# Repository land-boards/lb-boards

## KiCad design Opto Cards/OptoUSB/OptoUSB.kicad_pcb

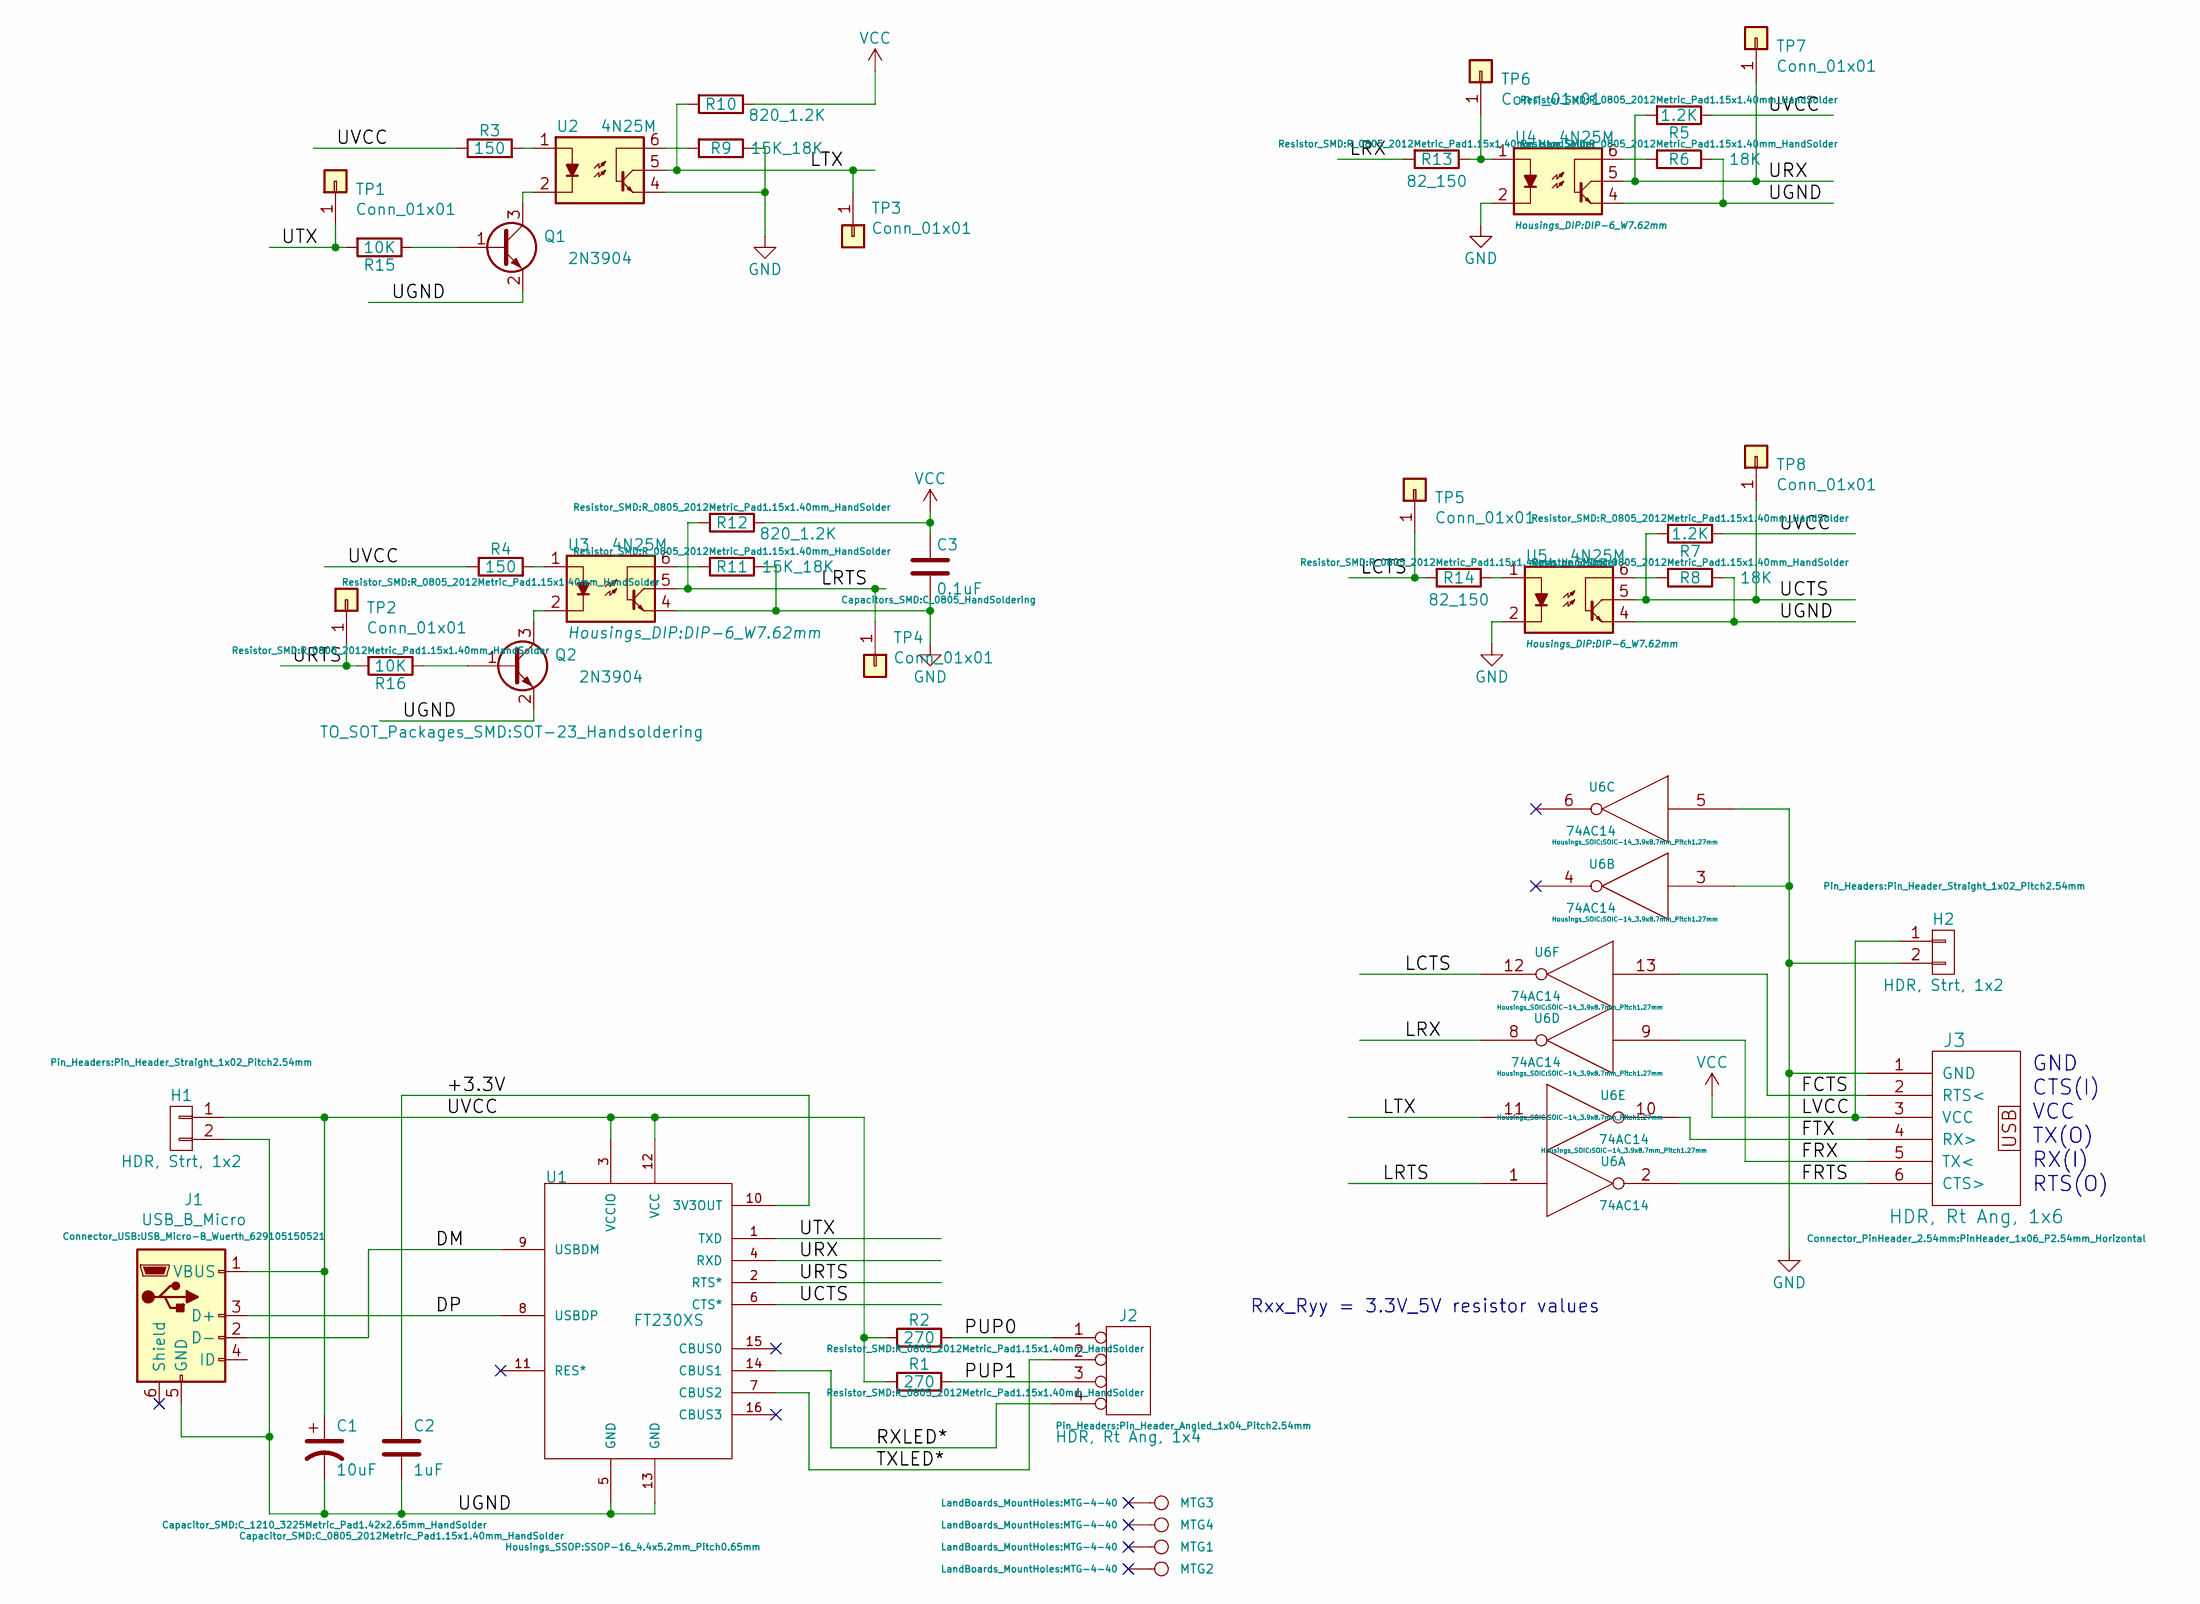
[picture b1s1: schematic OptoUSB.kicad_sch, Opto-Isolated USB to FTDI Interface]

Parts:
C1: 10uF; C_1210_3225Metric_Pad1.42x2.65mm_HandSolder; MfgPN CC121ZKY5V8BB106
C2: 1uF; C_0805_2012Metric_Pad1.15x1.40mm_HandSolder; MfgPN GRM155F51E104ZA1J
C3: 0.1uF; C_0805_HandSoldering
H1, H2: HDR, Strt, 1x2; Pin_Header_Straight_1x02_Pitch2.54mm
J1: USB_B_Micro; USB_Micro-B_Wuerth_629105150521
J2: HDR, Rt Ang, 1x4; Pin_Header_Angled_1x04_Pitch2.54mm
J3: HDR, Rt Ang, 1x6; PinHeader_1x06_P2.54mm_Horizontal
MTG1, MTG3: CONN_1; MTG-4-40; MfgPN N/A
MTG2, MTG4: CONN_1; MTG-4-40
Q1, Q2: 2N3904; SOT-23_Handsoldering
R1: 270; R_0805_2012Metric_Pad1.15x1.40mm_HandSolder
R2: 270; R_0805_2012Metric_Pad1.15x1.40mm_HandSolder; MfgPN CRG0805F270R
R3, R4: 150; R_0805_2012Metric_Pad1.15x1.40mm_HandSolder
R5, R7: 1.2K; R_0805_2012Metric_Pad1.15x1.40mm_HandSolder
R6, R8: 18K; R_0805_2012Metric_Pad1.15x1.40mm_HandSolder
R9, R11: 15K_18K; R_0805_2012Metric_Pad1.15x1.40mm_HandSolder
R10, R12: 820_1.2K; R_0805_2012Metric_Pad1.15x1.40mm_HandSolder
R13, R14: 82_150; R_0805_2012Metric_Pad1.15x1.40mm_HandSolder
R15, R16: 10K; R_0805_2012Metric_Pad1.15x1.40mm_HandSolder
TP1, TP2, TP3, TP4, TP5, TP6, TP7, TP8: Conn_01x01; PinHeader_1x01_P2.54mm_Vertical
U1: FT230XS; SSOP-16_4.4x5.2mm_Pitch0.65mm
U2, U3, U4, U5: 4N25M; DIP-6_W7.62mm
U6: 74AC14; SOIC-14_3.9x8.7mm_Pitch1.27mm

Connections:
/+3.3V: C2.1, U1.10 (3V3OUT)
/DM: J1.2 (D-), U1.9 (USBDM)
/DP: J1.3 (D+), U1.8 (USBDP)
/FCTS: J3.2 (RTS<), U6.13
/FRTS: J3.6 (CTS>), U6.2
/FRX: J3.5 (TX<), U6.9
/FTX: J3.4 (RX>), U6.10
/LCTS: R14.2, TP5.1, U6.12
/LRTS: R12.2, TP4.1, U3.5, U6.1
/LRX: R13.2, U6.8
/LTX: R10.2, TP3.1, U2.5, U6.11
/PUP0: J2.1, R2.2
/PUP1: J2.3, R1.2
/RXLED*: J2.4, U1.14 (CBUS1)
/TXLED*: J2.2, U1.7 (CBUS2)
/UCTS: R7.2, TP8.1, U1.6 (CTS*), U5.5
/UGND: C1.2, C2.2, H1.2, J1.5 (GND), Q1.2 (E), Q2.2 (E), R6.1, R8.1, U1.5 (GND), U1.13 (GND), U4.4, U5.4
/URTS: R16.2, TP2.1, U1.2 (RTS*)
/URX: R5.2, TP7.1, U1.4 (RXD), U4.5
/UTX: R15.2, TP1.1, U1.1 (TXD)
/UVCC: C1.1, H1.1, J1.1 (VBUS), R1.1, R2.1, R3.1, R4.1, R5.1, R7.1, U1.3 (VCCIO), U1.12 (VCC)
GND: C3.2, H2.2, J3.1 (GND), R9.1, R11.1, U2.4, U3.4, U4.2, U5.2, U6.3, U6.5, U6.7 (GND)
unnamed: Q1.1 (B), R15.1
unnamed: Q1.3 (C), U2.2
unnamed: Q2.1 (B), R16.1
unnamed: Q2.3 (C), U3.2
unnamed: R3.2, U2.1
unnamed: R4.2, U3.1
unnamed: R6.2, U4.6
unnamed: R8.2, U5.6
unnamed: R9.2, U2.6
unnamed: R11.2, U3.6
unnamed: R13.1, TP6.1, U4.1
unnamed: R14.1, U5.1
VCC: C3.1, H2.1, J3.3 (VCC), R10.1, R12.1, U6.14 (VCC)

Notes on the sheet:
Rxx_Ryy = 3.3V_5V resistor values
GND CTS(I) VCC TX(O) RX(I) RTS(O)

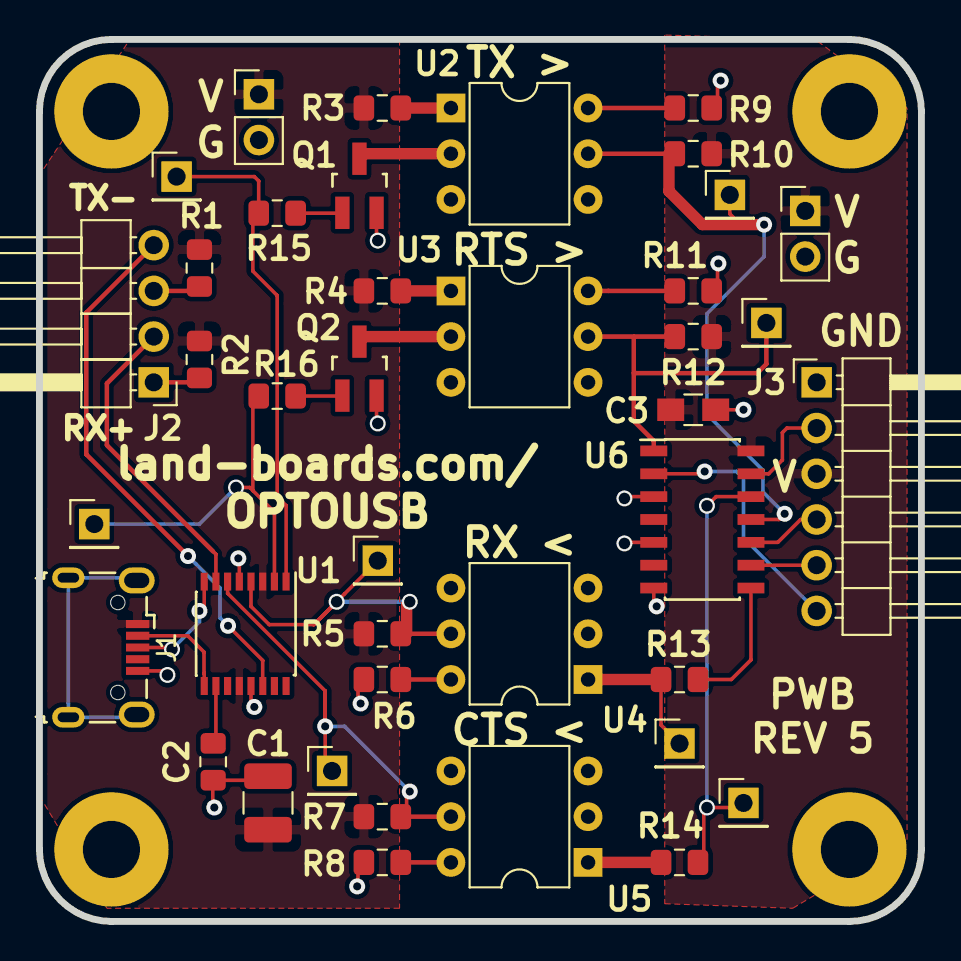
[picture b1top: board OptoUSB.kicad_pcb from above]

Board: 2 copper layers, 49.0 x 49.0 mm, 44 parts (0 on the bottom side), 35 nets.

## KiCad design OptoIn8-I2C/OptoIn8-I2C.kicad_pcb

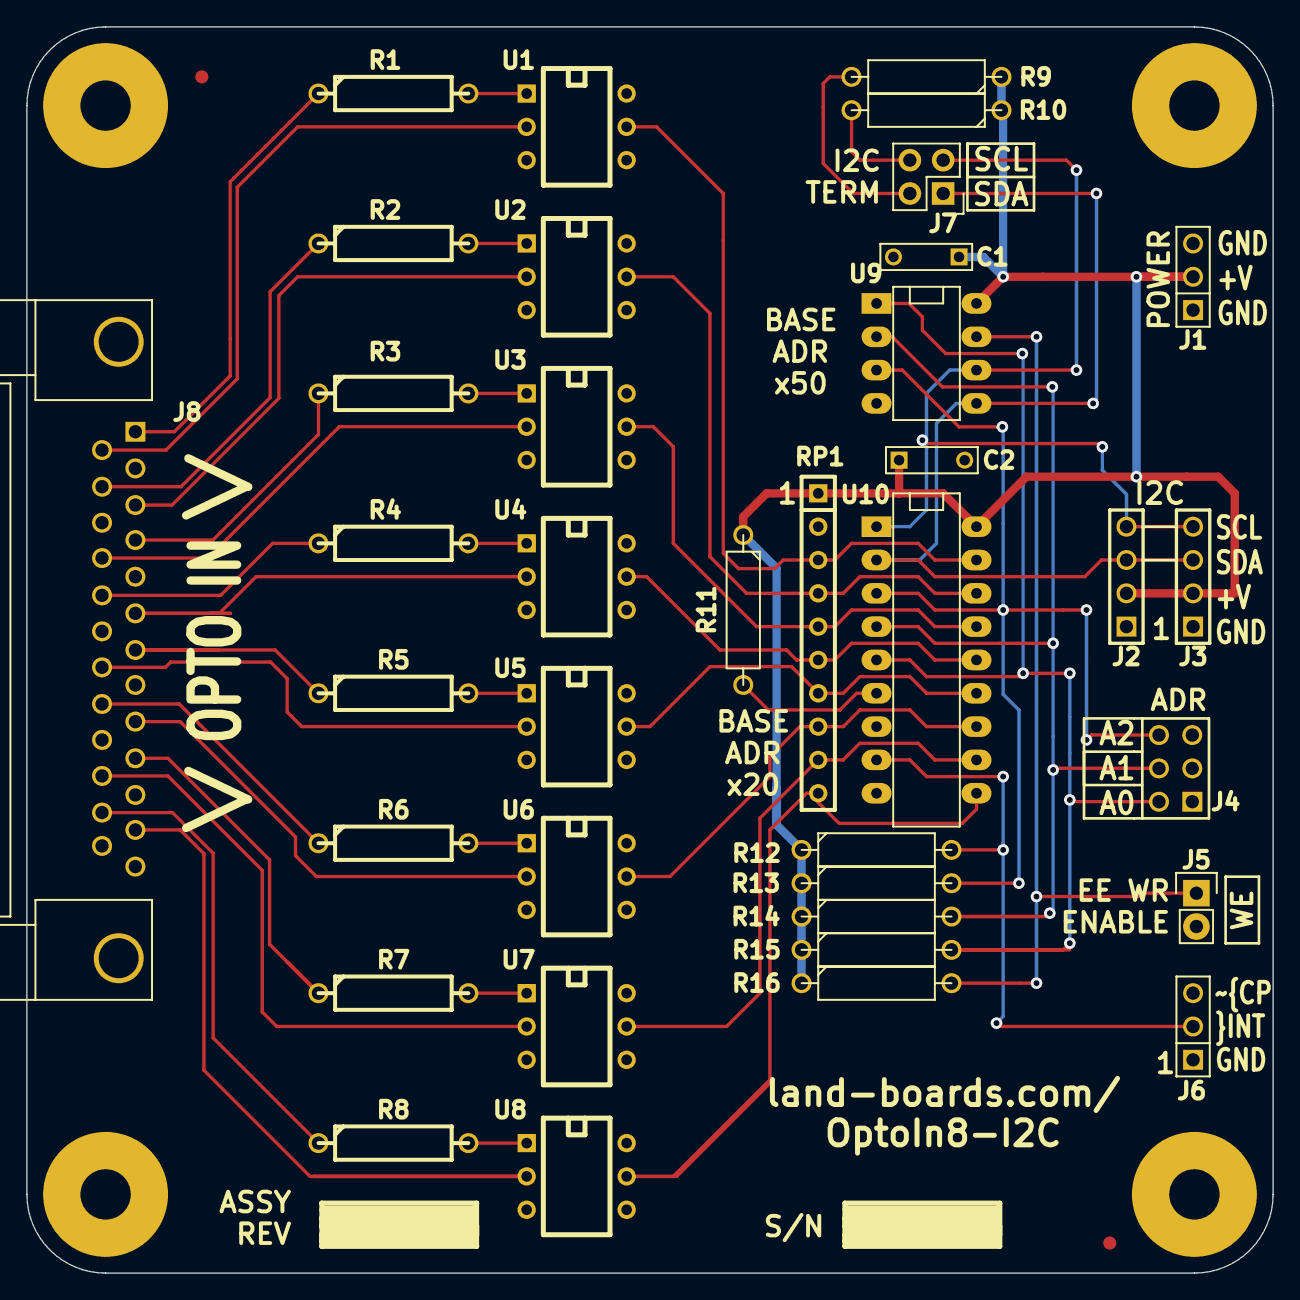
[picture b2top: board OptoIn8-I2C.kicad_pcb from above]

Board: 2 copper layers, 95.0 x 95.0 mm, 46 parts (0 on the bottom side), 44 nets.

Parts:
C1, C2: 0.1uF; C_Rect_L7_W2_P5
FID1, FID2: ADAFRUIT_FIDUCIAL; FIDUCIAL
J1, J6: CONN_3; PIN_ARRAY_3X1
J2, J3: CONN_4; PIN_ARRAY_4x1
J4: CONN_3X2; pin_array_3x2
J5: CONN_01X02; Pin_Header_Straight_1x02
J7: CONN_02X02; Pin_Header_Straight_2x02
J8: DB25; DB25MC
MTG1, MTG2, MTG3, MTG4: MTG_HOLE; MTG-6-32
R1, R2, R3, R4, R5, R6, R7, R8: 330; R4-5
R9, R10: 2.2K; R4-5
R11, R12, R13, R14, R15: 10K; R4-5
R16: 1K; R4-5
RP1: 4.7K-PACK; SIL-10
ST1: CONN_1; REV_BLOCK
ST2: REV-HIST; REV_BLOCK
TESTED: VAL**; TEST_BLK-REAR
U1, U2, U3, U4, U5, U6, U7, U8: 4N26; DIP-6__300
U9: 24C01; DIP-8__300_ELL
U10: MCP23008P; DIP-18__300_ELL

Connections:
/A0: J4.2, R15.2, U9.1, U10.5
/A1: J4.4, R14.2, U9.2, U10.4
/A2: J4.6, R13.2, U9.3, U10.3
/CH1-IN+: J8.1, R1.1
/CH1-IN-: J8.14, U1.2
/CH2-IN+: J8.15, R2.1
/CH2-IN-: J8.3, U2.2
/CH3-IN+: J8.4, R3.1
/CH3-IN-: J8.17, U3.2
/CH4-IN+: J8.18, R4.1
/CH4-IN-: J8.6, U4.2
/CH5-IN+: J8.7, R5.1
/CH5-IN-: J8.20, U5.2
/GND: C1.2, C2.2, J1.1, J1.3, J2.1, J3.1, J4.1, J4.3, J4.5, J5.2, J6.1, J6.3, U1.4, U2.4, U3.4, U4.4, U5.4, U6.4, U7.4, U8.4, U9.4, U10.9
/GP0: RP1.10, U8.5, U10.10
/GP1: RP1.9, U7.5, U10.11
/GP2: RP1.8, U6.5, U10.12
/GP3: RP1.7, U5.5, U10.13
/GP4: RP1.6, U4.5, U10.14
/GP5: RP1.5, U3.5, U10.15
/GP6: RP1.4, U2.5, U10.16
/GP7: RP1.3, U1.5, U10.17
/INT: J6.2, R12.2, U10.8
/SCL: J2.4, J3.4, J7.3, U9.6, U10.1
/SDA: J2.3, J3.3, J7.1, U9.5, U10.2
/VCC: C1.1, C2.1, J1.2, J2.2, J3.2, R9.1, R10.1, R11.1, R12.1, R13.1, R14.1, R15.1, R16.1, RP1.1, U9.8, U10.18
unnamed: J5.1, R16.2, U9.7
unnamed: J7.2, R9.2
unnamed: J7.4, R10.2
unnamed: J8.9, U6.2
unnamed: J8.10, R7.1
unnamed: J8.12, U8.2
unnamed: J8.21, R6.1
unnamed: J8.23, U7.2
unnamed: J8.24, R8.1
unnamed: R1.2, U1.1
unnamed: R2.2, U2.1
unnamed: R3.2, U3.1
unnamed: R4.2, U4.1
unnamed: R5.2, U5.1
unnamed: R6.2, U6.1
unnamed: R7.2, U7.1
unnamed: R8.2, U8.1
unnamed: R11.2, U10.6

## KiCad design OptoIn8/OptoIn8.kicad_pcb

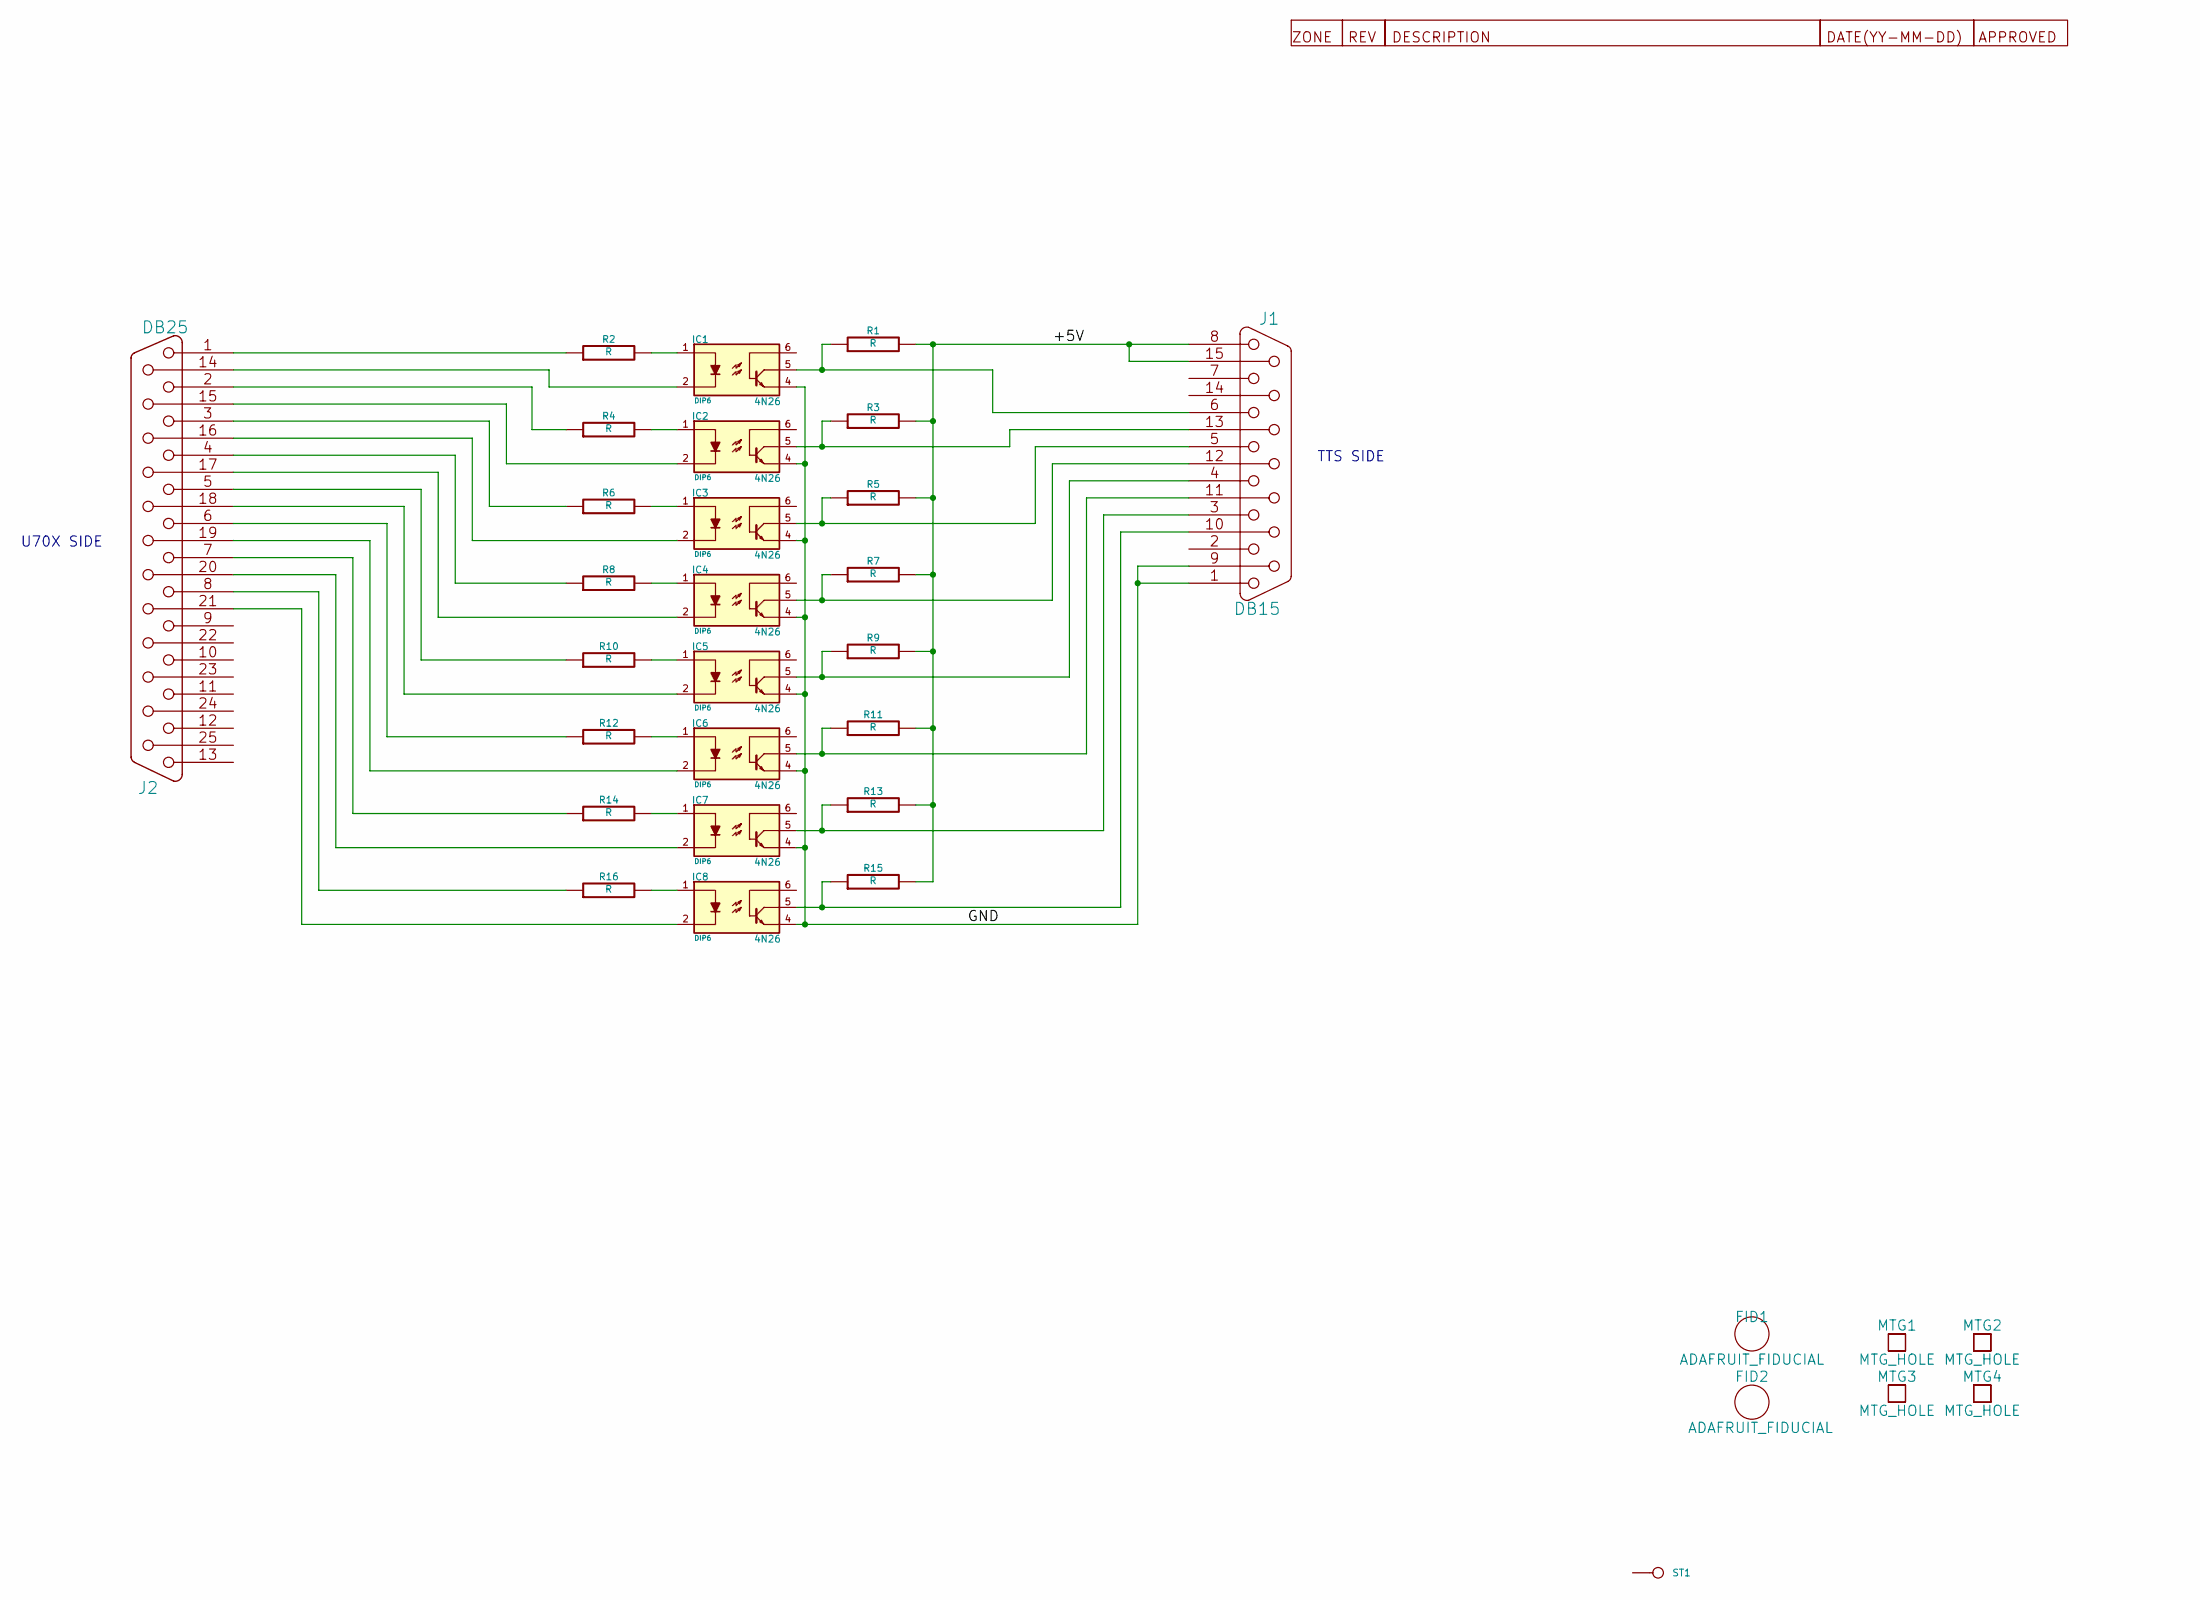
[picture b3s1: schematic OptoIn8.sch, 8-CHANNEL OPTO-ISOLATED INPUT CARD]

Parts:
FID1, FID2: ADAFRUIT_FIDUCIAL
IC1, IC2, IC3, IC4, IC5, IC6, IC7, IC8: 4N26; DIP6
J1: DB15
J2: DB25
MTG1, MTG2, MTG3, MTG4: MTG_HOLE
R1, R2, R3, R4, R5, R6, R7, R8, R9, R10, R11, R12, R13, R14, R15, R16: R
ST1: CONN_1
ST2: REV-HIST

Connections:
/+5V: J1.8, J1.15, R1.2, R3.2, R5.2, R7.2, R9.2, R11.2, R13.2, R15.2
/GND: IC1.4, IC2.4, IC3.4, IC4.4, IC5.4, IC6.4, IC7.4, IC8.4, J1.1, J1.9
unnamed: IC3.5, J1.5, R5.1
unnamed: IC4.5, J1.12, R7.1
unnamed: J2.8, R16.1
unnamed: IC8.2, J2.21
unnamed: IC2.5, J1.13, R3.1
unnamed: IC1.5, J1.6, R1.1
unnamed: IC8.5, J1.10, R15.1
unnamed: IC7.5, J1.3, R13.1
unnamed: IC5.5, J1.4, R9.1
unnamed: IC6.5, J1.11 (P111), R11.1
unnamed: J2.5, R10.1
unnamed: IC1.1, R2.2
unnamed: J2.4, R8.1
unnamed: J2.6, R12.1
unnamed: J2.7, R14.1
unnamed: IC8.1, R16.2
unnamed: J2.1, R2.1
unnamed: J2.2, R4.1
unnamed: J2.3, R6.1
unnamed: IC4.2, J2.17
unnamed: IC2.1, R4.2
unnamed: IC2.2, J2.15
unnamed: IC3.1, R6.2
unnamed: IC3.2, J2.16
unnamed: IC4.1, R8.2
unnamed: IC5.1, R10.2
unnamed: IC6.1, R12.2
unnamed: IC7.1, R14.2
unnamed: IC5.2, J2.18
unnamed: IC6.2, J2.19
unnamed: IC7.2, J2.20
unnamed: IC1.2, J2.14

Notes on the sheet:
TTS SIDE
U70X SIDE

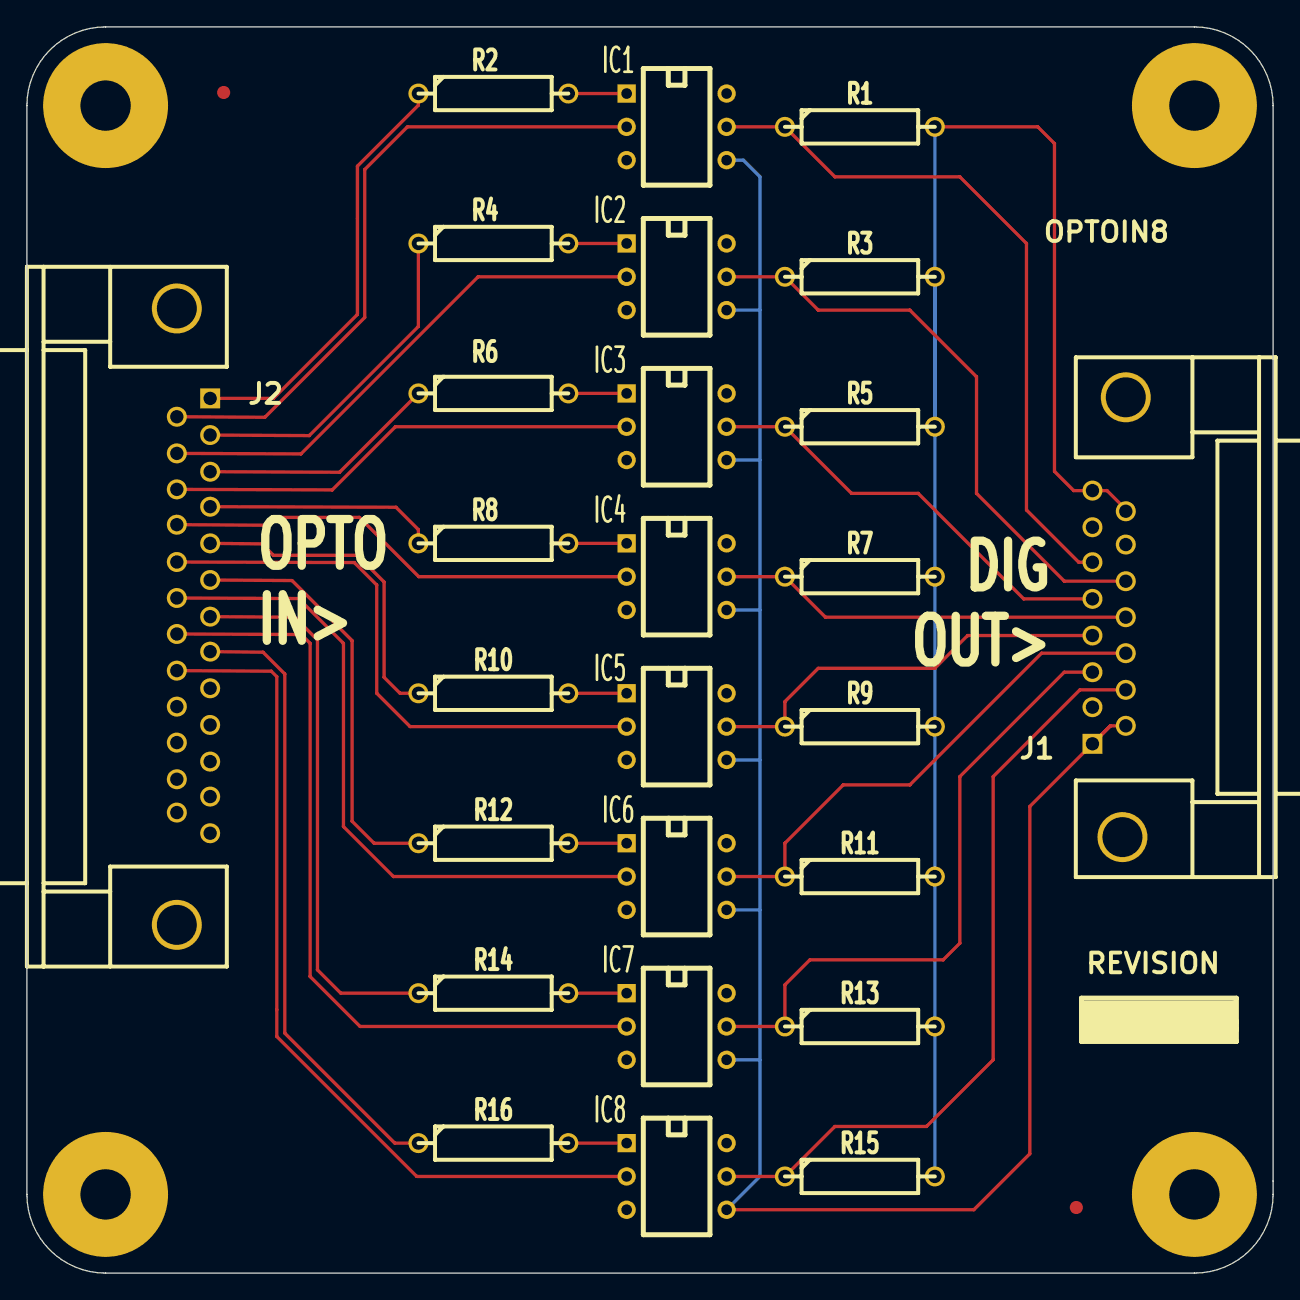
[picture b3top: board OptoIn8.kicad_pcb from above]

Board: 2 copper layers, 95.0 x 95.0 mm, 33 parts (0 on the bottom side), 34 nets.

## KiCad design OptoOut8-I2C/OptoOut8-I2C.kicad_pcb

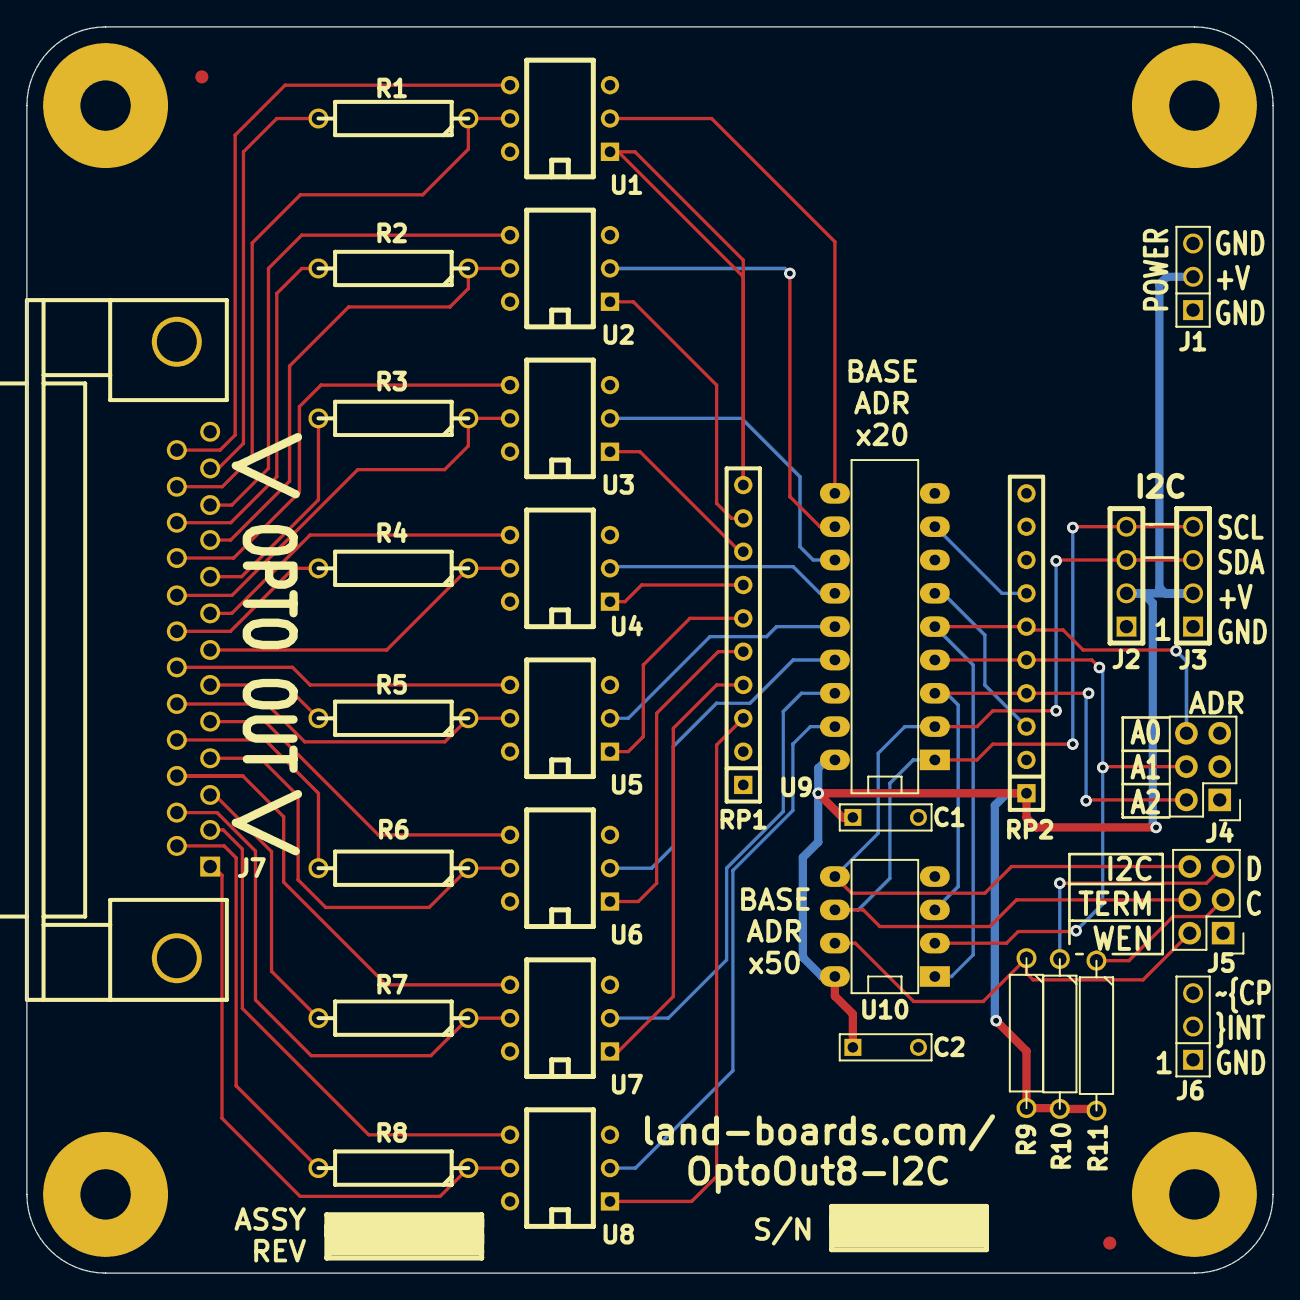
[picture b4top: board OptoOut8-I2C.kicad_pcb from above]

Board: 2 copper layers, 95.0 x 95.0 mm, 41 parts (0 on the bottom side), 52 nets.

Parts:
C1, C2: 0.1uF; C_Rect_L7_W2_P5
FID1, FID2: ADAFRUIT_FIDUCIAL; FIDUCIAL
J1, J6: CONN_3; PIN_ARRAY_3X1
J2, J3: CONN_4; pin_array_4x1
J4: CONN_3X2; Pin_Header_Straight_2x03
J5: CONN_02X03; Pin_Header_Straight_2x03
J7: DB25; DB25FC
MTG1, MTG2, MTG3, MTG4: MTG_HOLE; MTG-6-32
R1, R2, R3, R4, R5, R6, R7, R8: 330; R4-5
R9: 1K; R4-5
R10, R11: 2.2K; R4-5
RP1: 3.3K-RPACK; SIL-10
RP2: 4.7K-RPACK; SIL-10
ST1, ST2: CONN_1; REV_BLOCK
TESTED: VAL**; TEST_BLK-REAR
U1, U2, U3, U4, U5, U6, U7, U8: 4N26; DIP-6__300
U9: MCP23008P; DIP-18__300_ELL
U10: 24C01; DIP-8__300_ELL

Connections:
/A0: J4.6, RP2.6, U9.5, U10.1
/A1: J4.4, RP2.5, U9.4, U10.2
/A2: J4.2, RP2.4, U9.3, U10.3
/OPTO0-PLUS: J7.12, R1.2
/SCL: J2.4, J3.4, J5.4, U9.1, U10.6
/SDA: J2.3, J3.3, J5.6, U9.2, U10.5
/VCC: C1.1, C2.1, J1.2, J2.2, J3.2, R9.2, R10.2, R11.2, RP2.1, U9.18, U10.8
GND: C1.2, C2.2, J1.1, J1.3, J2.1, J3.1, J4.1, J4.3, J4.5, J5.1, J6.1, J6.3, U9.9, U10.4
unnamed: J5.2, R9.1, U10.7
unnamed: J5.3, R11.1
unnamed: J5.5, R10.1
unnamed: J7.1, R8.1, U8.5
unnamed: J7.2, U8.4
unnamed: J7.3, R7.2
unnamed: J7.4, R6.1, U6.5
unnamed: J7.5, U6.4
unnamed: J7.6, R5.2
unnamed: J7.7, R4.1, U4.5
unnamed: J7.8, U4.4
unnamed: J7.9, R3.2
unnamed: J7.10, R2.1, U2.5
unnamed: J7.11, U2.4
unnamed: J7.14, R8.2
unnamed: J7.15, R7.1, U7.5
unnamed: J7.16, U7.4
unnamed: J7.17, R6.2
unnamed: J7.18, R5.1, U5.5
unnamed: J7.19, U5.4
unnamed: J7.20, R4.2
unnamed: J7.21, R3.1, U3.5
unnamed: J7.22, U3.4
unnamed: J7.23, R2.2
unnamed: J7.24, R1.1, U1.5
unnamed: J7.25, U1.4
unnamed: RP1.3, U8.1
unnamed: RP1.4, U7.1
unnamed: RP1.5, U6.1
unnamed: RP1.6, U5.1
unnamed: RP1.7, U4.1
unnamed: RP1.8, U3.1
unnamed: RP1.9, U2.1
unnamed: RP1.10, U1.1
unnamed: RP2.3, U9.6
unnamed: RP2.7, U9.8
unnamed: U1.2, U9.10
unnamed: U2.2, U9.11
unnamed: U3.2, U9.12
unnamed: U4.2, U9.13
unnamed: U5.2, U9.14
unnamed: U6.2, U9.15
unnamed: U7.2, U9.16
unnamed: U8.2, U9.17

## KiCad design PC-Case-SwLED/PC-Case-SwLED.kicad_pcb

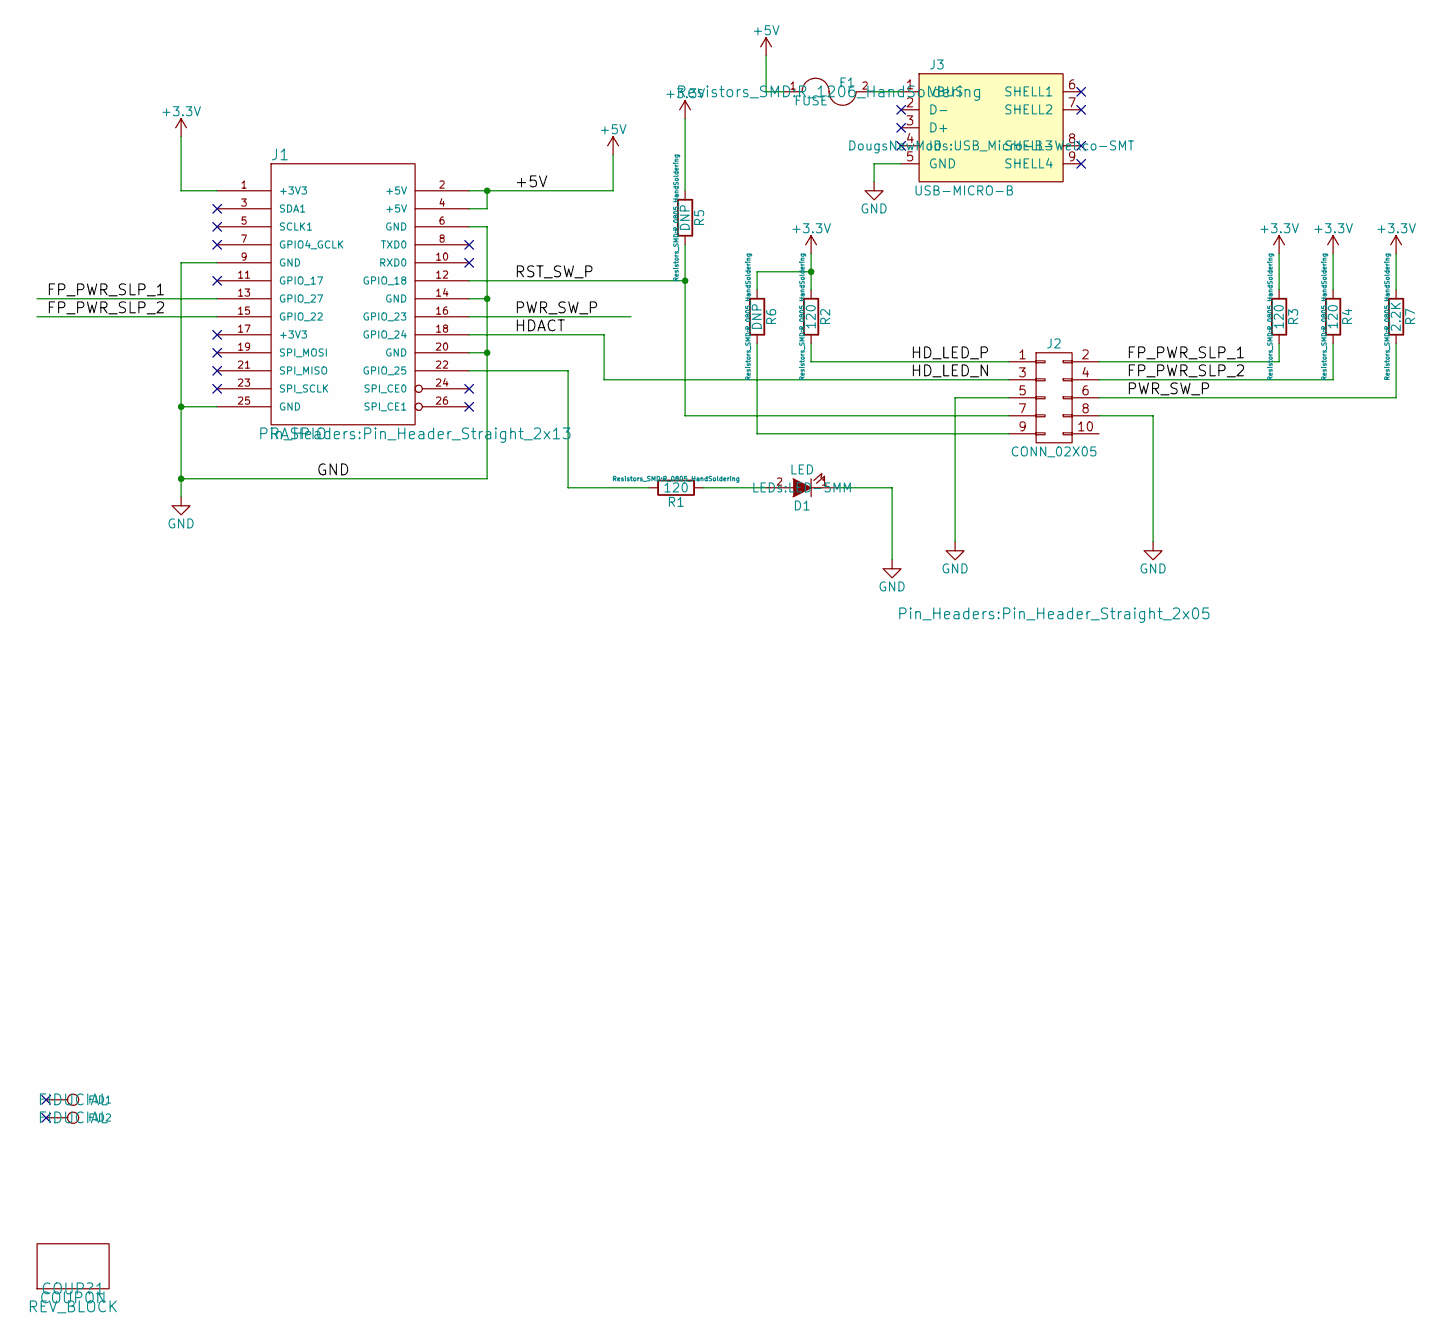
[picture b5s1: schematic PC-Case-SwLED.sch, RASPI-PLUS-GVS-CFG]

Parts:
COUP?1: COUPON; REV_BLOCK
D1: LED; LED-5MM
F1: FUSE; R_1206_HandSoldering
FID1, FID2: CONN_1; FIDUCIAL
J1: RASPIO; Pin_Header_Straight_2x13
J2: CONN_02X05; Pin_Header_Straight_2x05
J3: USB-MICRO-B; USB_Micro-B-Wellco-SMT
R1, R2, R3, R4: 120; R_0805_HandSoldering
R5, R6: DNP; R_0805_HandSoldering
R7: 2.2K; R_0805_HandSoldering

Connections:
+3V3: J1.1 (+3V3), R2.1, R3.1, R4.1, R5.1, R6.1, R7.1
+5V: F1.1, J1.2 (+5V), J1.4 (+5V)
/FP_PWR_SLP_1: J1.13 (GPIO_27), J2.2, R3.2
/FP_PWR_SLP_2: J1.15 (GPIO_22), J2.4, R4.2
/HDACT: J1.18 (GPIO_24), J2.3
/HD_LED_P: J2.1, R2.2
/PWR_SW_P: J1.16 (GPIO_23), J2.6, R7.2
/RST_SW_P: J1.12 (GPIO_18), J2.7, R5.2
GND: D1.1 (K), J1.6 (GND), J1.9 (GND), J1.14 (GND), J1.20 (GND), J1.25 (GND), J2.5, J2.8, J3.5 (GND)
unnamed: D1.2 (A), R1.1
unnamed: F1.2, J3.1 (VBUS)
unnamed: J1.22 (GPIO_25), R1.2
unnamed: J2.9, R6.2

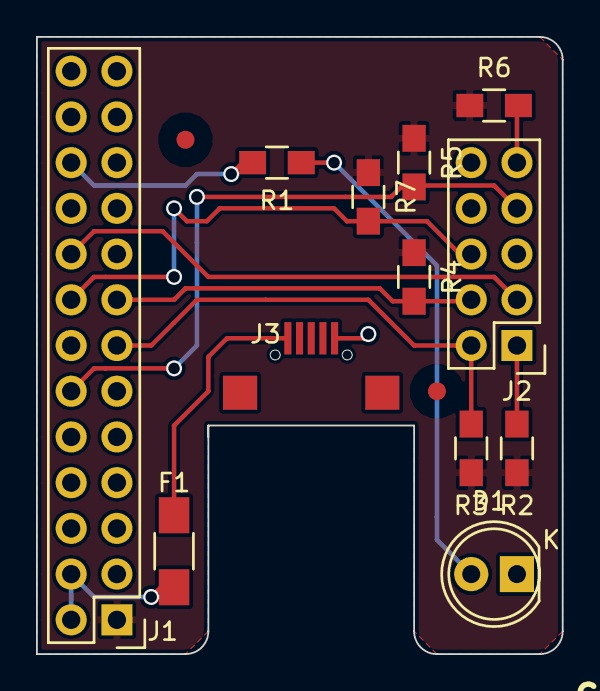
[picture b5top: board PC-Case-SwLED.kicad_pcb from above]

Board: 2 copper layers, 29.2 x 34.3 mm, 16 parts (1 on the bottom side), 13 nets.

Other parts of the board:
TEST: COUPON; REV_BLOCK
